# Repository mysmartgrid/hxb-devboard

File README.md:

hxb-devboard
============
This a hexabus module based on the hardware published at https://github.com/mysmartgrid/hexabus.

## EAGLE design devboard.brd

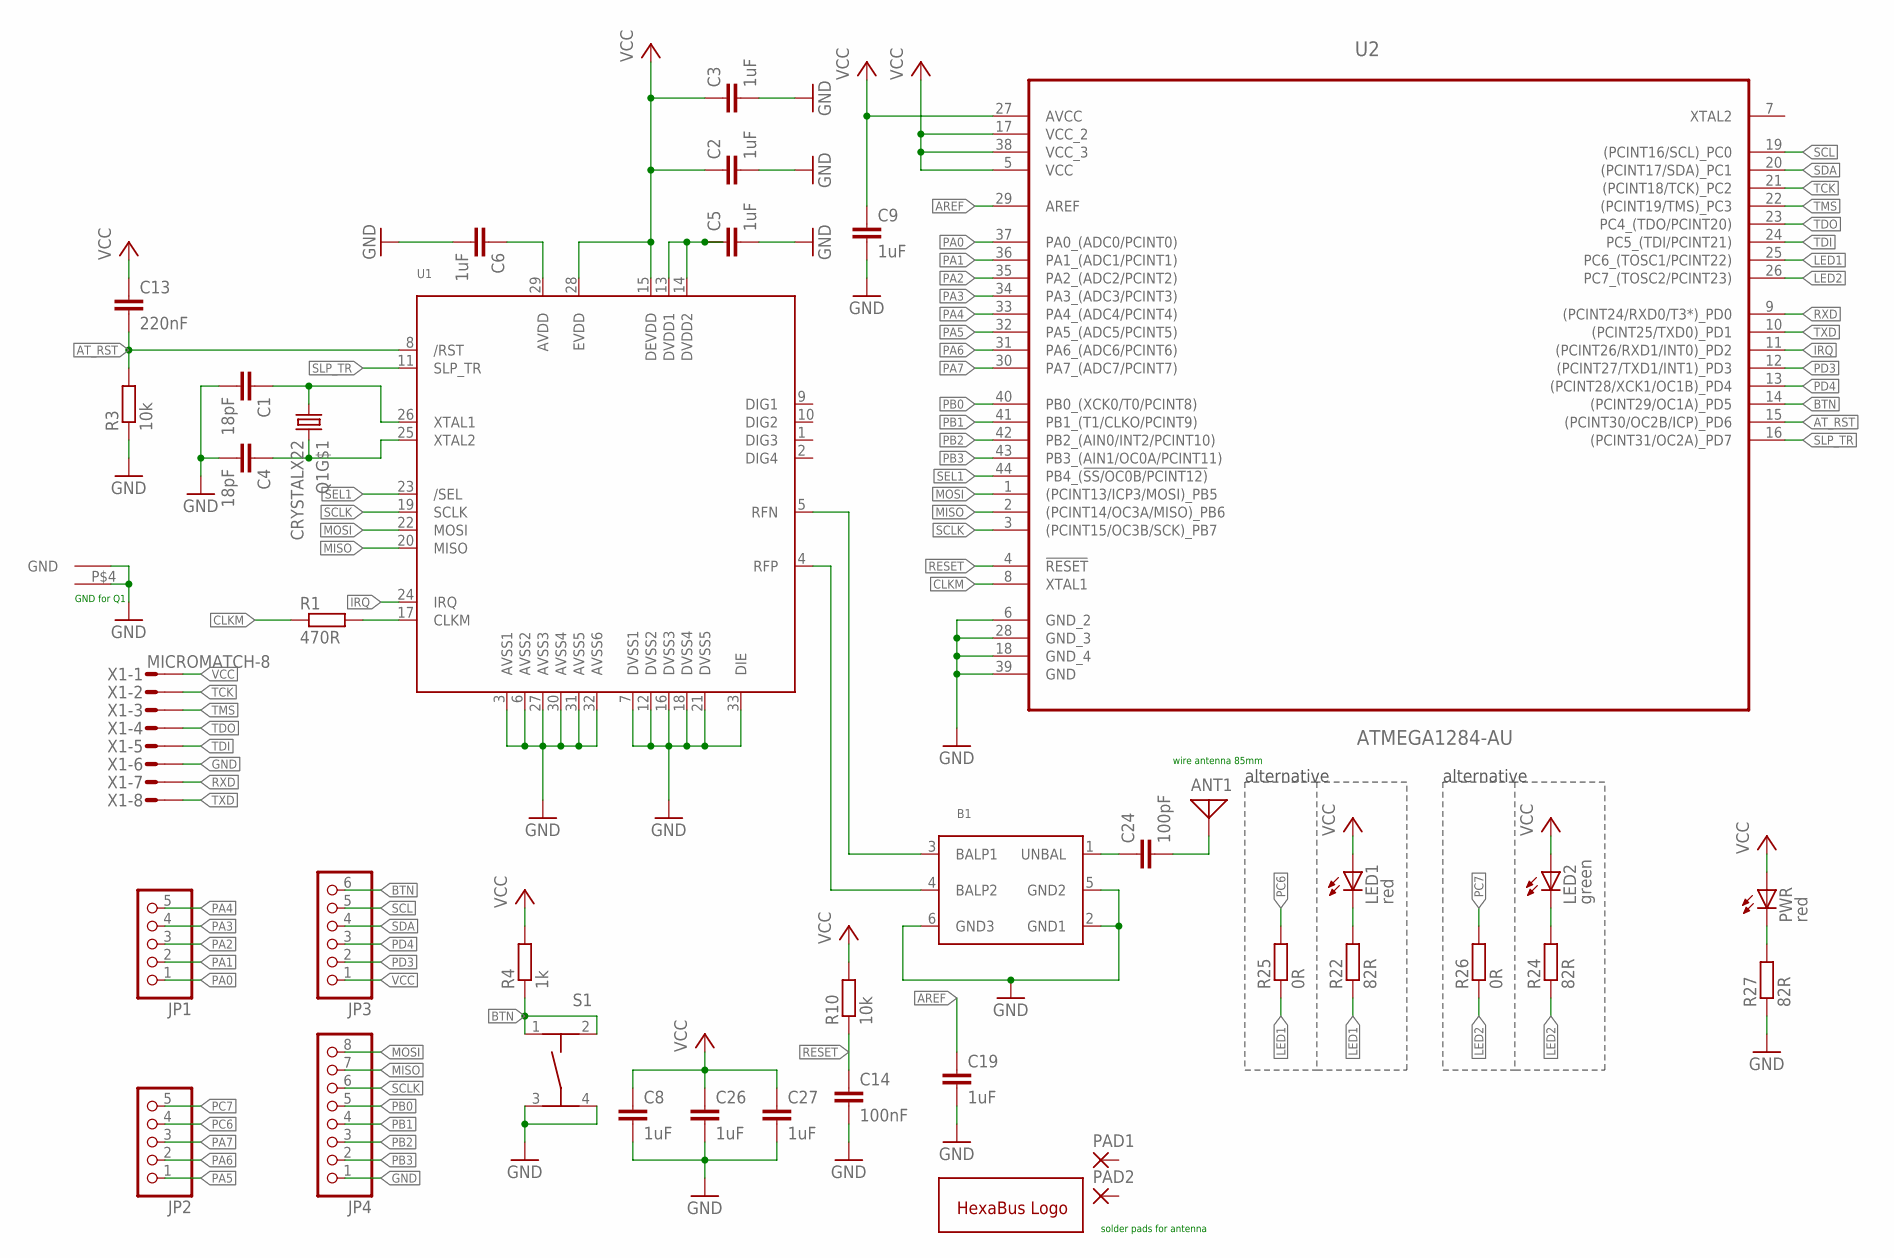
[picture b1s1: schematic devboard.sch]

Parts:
ANT1: ANTENNA; PAD-01
B1: BALUN+LP; BALUN0805
C1, C4: 18pF; C0603
C2, C3, C5, C6, C8, C9, C19, C26, C27: 1uF; C0603
C13: 220nF; C0603
C14: 100nF; C0603
C24: 100pF; C0603
JP1, JP2: PINHD-1X5; 1X05
JP3: PINHD-1X6; 1X06
JP4: PINHD-1X8; 1X08
LED1: red; CHIP-LED0603
LED2: green; CHIP-LED0603
PAD1, PAD2: SMD2; SMD1,27-2,54
PWR: red; CHIP-LED0603
Q1: CRYSTALX22; X22
R1: 470R; R0603
R3, R10: 10k; R0603
R4: 1k; R0603
R22, R24, R27: 82R; R0603
R25, R26: 0R; R0603
S1: TASTER-9314_SMD
U1: AT86RF212; 32QN2
U2: ATMEGA1284-AU; QFP80P1200X1200X120-44N
U$1: HEXAKRAKE
X1: MICROMATCH-8

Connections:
!RESET: C14.1, R10.1, U2.4 (!RESET)
AREF: C19.1, U2.29 (AREF)
AT_RST: C13.2, R3.2, U1.8 (/RST), U2.15 ((PCINT30/OC2B/ICP)_PD6)
BTN: JP3.6, R4.1, S1.1, S1.2, U2.14 ((PCINT29/OC1A)_PD5)
CLKM: R1.1, U2.8 (XTAL1)
GND: B1.2 (GND1), B1.5 (GND2), B1.6 (GND3), C1.2, C2.2, C3.2, C4.2, C5.2, C6.2, C8.2, C9.2, C14.2, C19.2, C26.2, C27.2, JP4.1, Q1.P$2 (GND), Q1.P$4 (GND1), R3.1, R27.1, S1.3, S1.4, U1.3 (AVSS1), U1.6 (AVSS2), U1.7 (DVSS1), U1.12 (DVSS2), U1.16 (DVSS3), U1.18 (DVSS4), U1.21 (DVSS5), U1.27 (AVSS3), U1.30 (AVSS4), U1.31 (AVSS5), U1.32 (AVSS6), U1.33 (DIE), U2.6 (GND_2), U2.18 (GND_4), U2.28 (GND_3), U2.39 (GND), X1.6
IRQ: U1.24 (IRQ), U2.11 ((PCINT26/RXD1/INT0)_PD2)
LED1: R22.1, R25.1, U2.25 (PC6_(TOSC1/PCINT22))
LED2: R24.1, R26.1, U2.26 (PC7_(TOSC2/PCINT23))
MISO: JP4.7, U1.20 (MISO), U2.2 ((PCINT14/OC3A/MISO)_PB6)
MOSI: JP4.8, U1.22 (MOSI), U2.1 ((PCINT13/ICP3/MOSI)_PB5)
unnamed: C6.1, U1.29 (AVDD)
unnamed: C5.1, U1.13 (DVDD1), U1.14 (DVDD2)
unnamed: LED1.C, R22.2
unnamed: R1.2, U1.17 (CLKM)
unnamed: LED2.C, R24.2
unnamed: B1.3 (BALP1), U1.5 (RFN)
unnamed: B1.4 (BALP2), U1.4 (RFP)
unnamed: C1.1, Q1.P$1 (1), U1.26 (XTAL1)
unnamed: C4.1, Q1.P$3 (2), U1.25 (XTAL2)
unnamed: PWR.C, R27.2
unnamed: B1.1 (UNBAL), C24.1
unnamed: ANT1.1, C24.2
PA0: JP1.1, U2.37 (PA0_(ADC0/PCINT0))
PA1: JP1.2, U2.36 (PA1_(ADC1/PCINT1))
PA2: JP1.3, U2.35 (PA2_(ADC2/PCINT2))
PA3: JP1.4, U2.34 (PA3_(ADC3/PCINT3))
PA4: JP1.5, U2.33 (PA4_(ADC4/PCINT4))
PA5: JP2.1, U2.32 (PA5_(ADC5/PCINT5))
PA6: JP2.2, U2.31 (PA6_(ADC6/PCINT6))
PA7: JP2.3, U2.30 (PA7_(ADC7/PCINT7))
PB0: JP4.5, U2.40 (PB0_(XCK0/T0/PCINT8))
PB1: JP4.4, U2.41 (PB1_(T1/CLKO/PCINT9))
PB2: JP4.3, U2.42 (PB2_(AIN0/INT2/PCINT10))
PB3: JP4.2, U2.43 (PB3_(AIN1/OC0A/PCINT11))
PC6: JP2.4, R25.2
PC7: JP2.5, R26.2
PD3: JP3.2, U2.12 ((PCINT27/TXD1/INT1)_PD3)
PD4: JP3.3, U2.13 ((PCINT28/XCK1/OC1B)_PD4)
RXD: U2.9 ((PCINT24/RXD0/T3*)_PD0), X1.7
SCL: JP3.5, U2.19 ((PCINT16/SCL)_PC0)
SCLK: JP4.6, U1.19 (SCLK), U2.3 ((PCINT15/OC3B/SCK)_PB7)
SDA: JP3.4, U2.20 ((PCINT17/SDA)_PC1)
SEL1: U1.23 (/SEL), U2.44 (PB4_(!SS/OC0B/PCINT12))
SLP_TR: U1.11 (SLP_TR), U2.16 ((PCINT31/OC2A)_PD7)
TCK: U2.21 ((PCINT18/TCK)_PC2), X1.2
TDI: U2.24 (PC5_(TDI/PCINT21)), X1.5
TDO: U2.23 (PC4_(TDO/PCINT20)), X1.4
TMS: U2.22 ((PCINT19/TMS)_PC3), X1.3
TXD: U2.10 ((PCINT25/TXD0)_PD1), X1.8
VCC: C2.1, C3.1, C8.1, C9.1, C13.1, C26.1, C27.1, JP3.1, LED1.A, LED2.A, PWR.A, R4.2, R10.2, U1.15 (DEVDD), U1.28 (EVDD), U2.5 (VCC), U2.17 (VCC_2), U2.27 (AVCC), U2.38 (VCC_3), X1.1

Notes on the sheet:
GND for Q1
wire antenna 85mm
solder pads for antenna
alternative

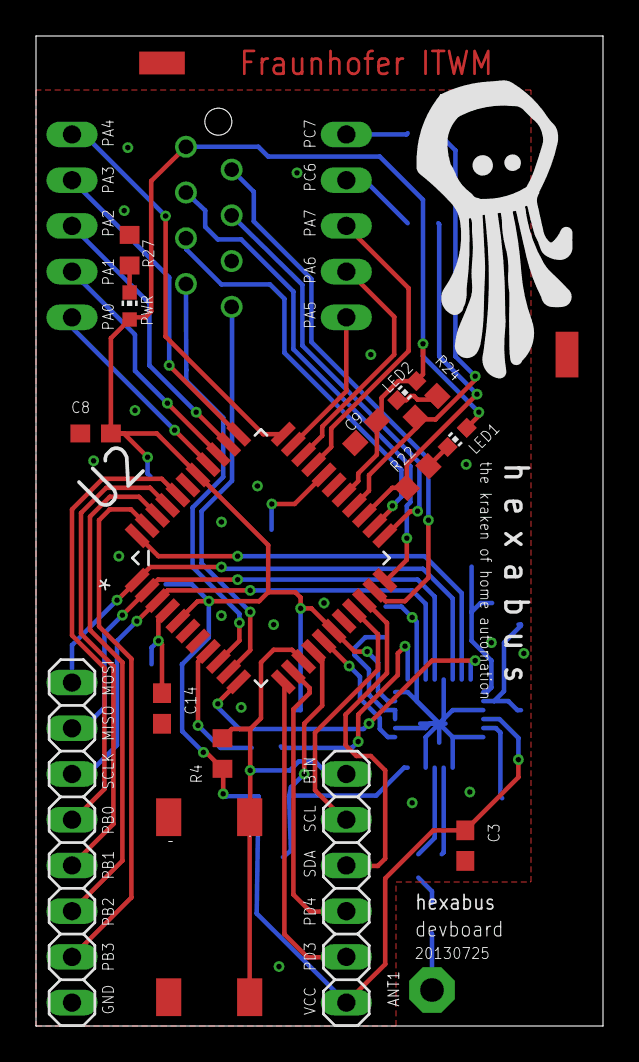
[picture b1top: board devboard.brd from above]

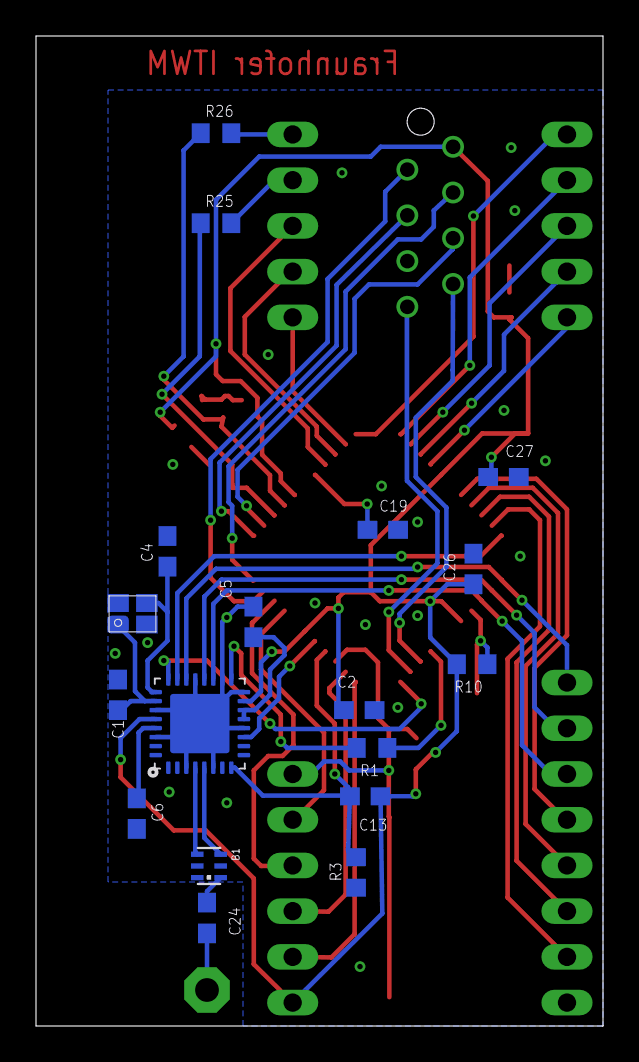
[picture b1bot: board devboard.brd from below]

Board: 2 copper layers, 31.5 x 55.0 mm, 40 parts (18 on the bottom side), 51 nets.

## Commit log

2012-03-28 schematic almost done
2012-03-29 changes on schematic, started routing
2012-03-29 routing...
2012-03-29 finished the routing and added notes
2012-03-30 added BOM
2012-11-21 started redoing of the wires
2012-11-22 added gitignore
2012-11-22 resized board
2012-11-22 nicer routing
2012-11-22 moved some vias
2012-11-22 redid routing for better placement of the radio chip
2012-11-23 added artwork, minor improvements
2012-11-27 further improvements
2012-12-10 changed label of R4 to top side
2012-12-13 added LED colors
2012-12-13 improved placement layer
2012-12-14 changed C2, C3 from 0805 to 0603
2012-12-14 minor changes in placement print
2012-12-17 corrected errors in placement print for PAx
2013-04-17 added EAGLE library
2013-04-19 changed JP4 to 8 pin
2013-04-25 updated to include MISO,MOSI,SCLK to external pins
2013-07-25 changed C13, C14 to 0603
2014-03-27 changed atmega to nonambiguous package
2014-03-27 redrawn some wires that were lost due to swapping the atmega
2014-03-27 missed a detail...
2014-03-28 added note for C1, C4
2014-03-28 updated bom
